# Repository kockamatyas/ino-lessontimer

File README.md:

# ino-lessontimer

Arduino program that counts down school lesson time

## Assembly

The following is required in order to assemble the device:

- Arduino Nano
- TM1637 display
- 4 buttons (**MINUS**, **PLUS**, **SET** and **SHOW**)
- An RGB led (+resistors, if required)

Assemble the component as described in the schematic file `kicad/ino-lessontimer/ino-lessontimer.kicad_sch`.
You can also use the PCB file (`kicad/ino-lessontimer/ino-lessontimer.kicad_pcb`) to make a circuit board.
If you want to change the pin bindings in the schematic or in the PCB, don't forget to do so in `Config.hpp`.

## Timetable

Follow the instructions in `sampleTimetable.hpp` to make your custom `Timetable.hpp` file.

## Usage

Lessontimer has two phases.

### Selection

Use the **PLUS** and **MINUS** buttons to select a day in the timetable. Then confirm the selection by  
pressing the **SET** button. Press the **SET** button one more time exactly at the beginning of the schedule.

### Countdown

After starting the countdown, you can select three modes, which you can switch between with the **SET** button. In each mode, the display can be turned on or off with the **SHOW** button. Leaving the display on even when not in active use may result in the device turning off prematurely due to low battery.

#### Lesson/break mode

After switching to this mode, you will see the time remaining until the end of the lesson/break, if the current segment is not a lesson/break, the display is blank.

#### Long break mode

When there is no longbreak currently in progress, you will see the time remaining until the longbreak starts. You will then see the time remaining until the end of the longbreak. After this time, the display will be blank.

#### Schedule end mode

Countdown to the end of the schedule.

## Library notice

This project uses the TM1637, a third-party library, which is distributed under the terms of the GNU Lesser General Public License (LGPL) version 3.  
You can find more information about the library and its licensing terms at <https://github.com/avishorp/TM1637>.

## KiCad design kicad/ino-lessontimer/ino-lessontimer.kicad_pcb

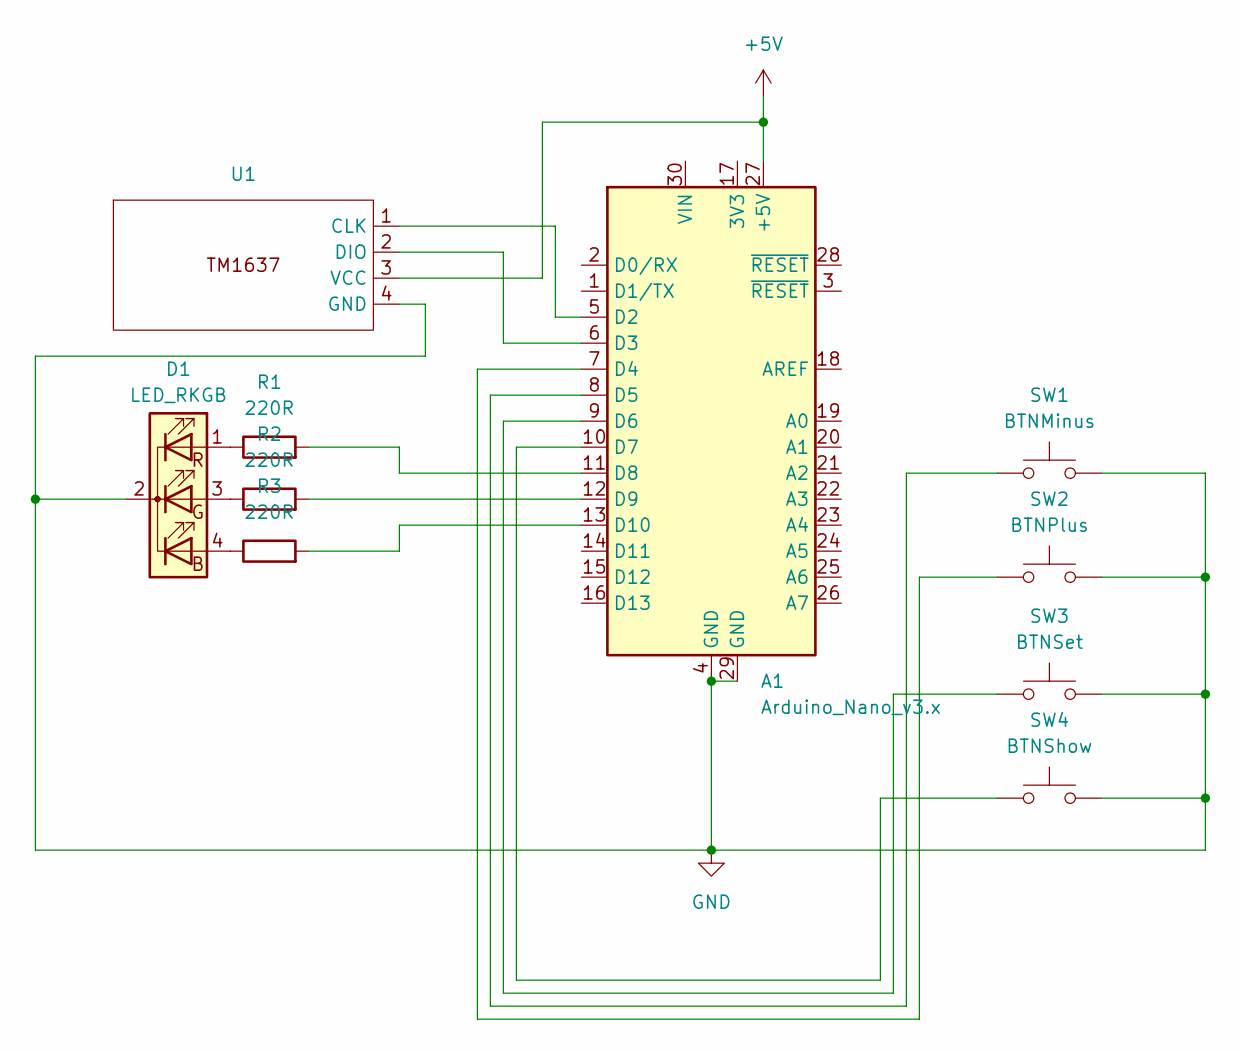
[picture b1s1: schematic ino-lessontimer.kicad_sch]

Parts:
A1: Arduino_Nano_v3.x; Arduino_Nano
D1: LED_RKGB; LED_D5.0mm-4_RGB
R1, R2, R3: 220R; R_Axial_DIN0207_L6.3mm_D2.5mm_P7.62mm_Horizontal
SW1: BTNMinus; Push_E-Switch_KS01Q01
SW2: BTNPlus; Push_E-Switch_KS01Q01
SW3: BTNSet; Push_E-Switch_KS01Q01
SW4: BTNShow; Push_E-Switch_KS01Q01
U1: TM1637

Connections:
+5V: A1.27 (+5V), U1.3 (VCC)
GND: A1.4 (GND), A1.29 (GND), D1.2 (K), SW1.2, SW2.2, SW3.2, SW4.2, U1.4 (GND)
unnamed: A1.5 (D2), U1.1 (CLK)
unnamed: A1.6 (D3), U1.2 (DIO)
unnamed: A1.7 (D4), SW2.1
unnamed: A1.8 (D5), SW1.1
unnamed: A1.9 (D6), SW3.1
unnamed: A1.10 (D7), SW4.1
unnamed: A1.11 (D8), R1.2
unnamed: A1.12 (D9), R2.2
unnamed: A1.13 (D10), R3.2
unnamed: D1.4 (BA), R3.1
unnamed: D1.3 (GA), R2.1
unnamed: D1.1 (RA), R1.1

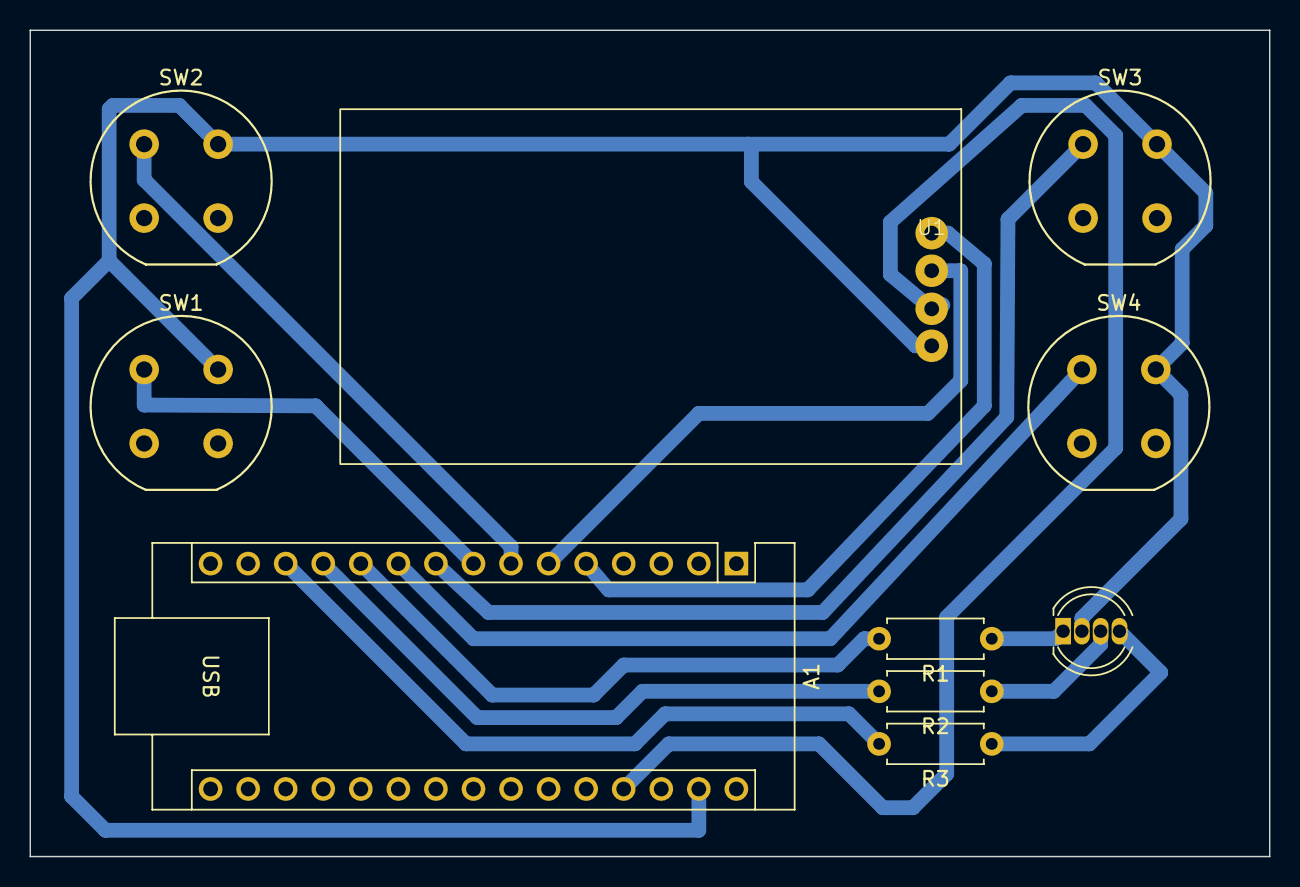
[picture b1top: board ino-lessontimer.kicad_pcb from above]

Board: 2 copper layers, 83.8 x 55.9 mm, 10 parts (0 on the bottom side), 14 nets.

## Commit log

2023-09-08 Added a library install script and the TM1637 libary to it
2023-09-08 Added .vscode to .gitignore
2023-09-08 Created ClockTime
2023-09-08 Added the ClockTime struct
2023-09-08 Changed ClockTime properties to unsigned long
2023-09-08 Added msToClockTime
2023-09-09 Added the display
2023-09-09 Added displayClockTime
2023-09-09 Improved formatting
2023-09-10 Created Schedule.hpp
2023-09-10 Added the ScheduleSegment struct
2023-09-10 Renamed Schedule.hpp to ScheduleSegment.hpp
2023-09-10 Renamed macros for ScheduleSegment.hpp
2023-09-10 Moved ScheduleSegment type enum outside of the struct as ScheduleSegmentType
2023-09-10 Added None as a ScheduleSegmentType
2023-09-10 Moved ScheduleSegment.hpp into its own folder, added ScheduleSegment.cpp
2023-09-10 Added the mkScheduleSegment function
2023-09-10 Renamed length to duration_ms
2023-09-10 Added sampleTimetable.hpp
2023-09-11 Added Timetable.hpp to .gitignore
2023-09-11 Fixed arithmetic issue in displayClockTime
2023-09-12 Added build to .gitignore
2023-09-12 Added encodeDigit calls to displayClockTime
2023-09-12 Renamed sketch.ino to ino-lessontimer.ino
2023-09-12 Moved ClockTime.* to root dir
2023-09-12 Moved ScheduleSegment.* to root dir
2023-09-12 Fixed ClockTime.hpp include in ino-lessontimer.ino
2023-09-12 Included Arduino.h in ino-lessontimer.ino
2023-09-13 Changed DISPLAY_BRIGHTNESS to 2
2023-09-13 Fixed calculation issue in displayClockTime
2023-09-13 Fixed typecast in displayClockTime
2023-09-13 Added the button class
2023-09-13 Fixed Button::isPressed
2023-09-13 Removed unnecessary Button::awaitPress function
2023-09-13 Added the RGBLed class
2023-09-13 Added button and RGBLed pins to ino-lessontimer.ino
2023-09-14 Added the buttons and the RGB led
2023-09-14 Added begin calls to the setup function
2023-09-14 Added the Mode enum and RGB colors for the modes
2023-09-14 Modified mode names - fixed LongBreak redeclaration
2023-09-14 Added the schedule selector
2023-09-14 Switched to the custom Dual-Owner Software License (Version 1.0)
2023-09-14 Added library notice to README.md
2023-09-15 Replaced delay with button release await
2023-09-15 Joined Lesson and Break to LessonBreak
2023-09-15 Modified the RGBLed::set function to test argument using hardcoded bytes
2023-09-15 Added usage to README.md
2023-09-15 Changed mode colors
2023-09-15 Added loop
2023-09-16 Added a better sampleTimetable.hpp file
2023-09-16 Exported config from ino-lessontimer.ino to Config.hpp, renamed color macros
2023-09-16 Added assembly and timetable sections in README.md
2023-09-16 Fixed SHOW button not preventing interaction
2023-10-02 Reduced total memory size of ClockTime
2023-10-02 Moved release await on SHOW button press
2023-11-02 Added .gitignore to kicad dir
2023-11-02 Fixed .gitignore including unwanted files
2023-11-02 Added symbol library table exception to .gitignore
2023-11-02 Added the custom TM1637 symbol
2023-11-02 Added the schema
2023-11-02 Fixed non-relative library URI in sym-lib-table
2023-11-03 Numbered and moved pins in TM1637 symbol
2023-11-03 Updated schema to fixed TM1637
2023-11-03 Replaced MODE_LED symbol in the schema
2023-11-03 Added PCB
2023-11-04 Fixed PCB track spacing
2023-11-06 Changed pin binds in config to align with the schematic
2023-11-08 Updated assembly documentation to reference kicad files
